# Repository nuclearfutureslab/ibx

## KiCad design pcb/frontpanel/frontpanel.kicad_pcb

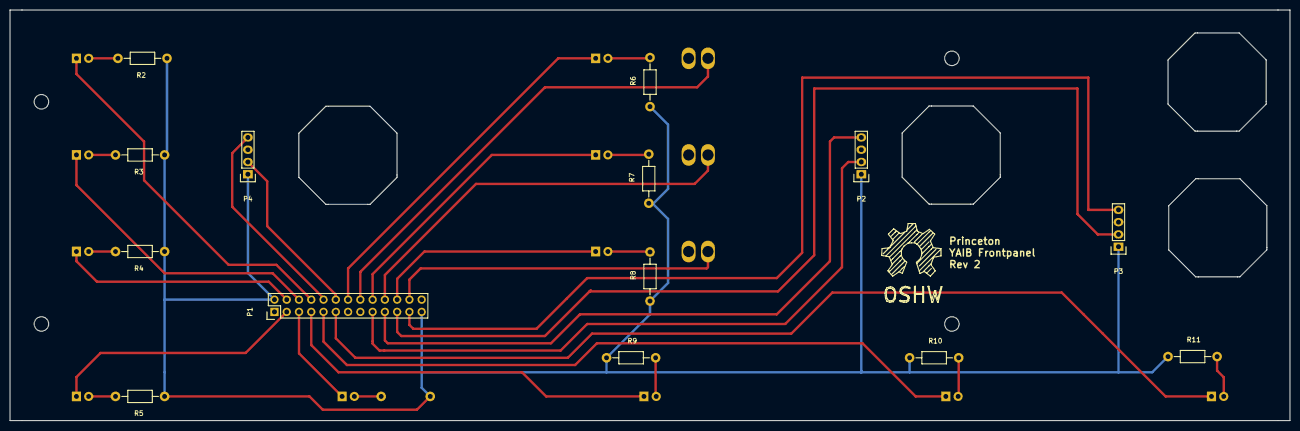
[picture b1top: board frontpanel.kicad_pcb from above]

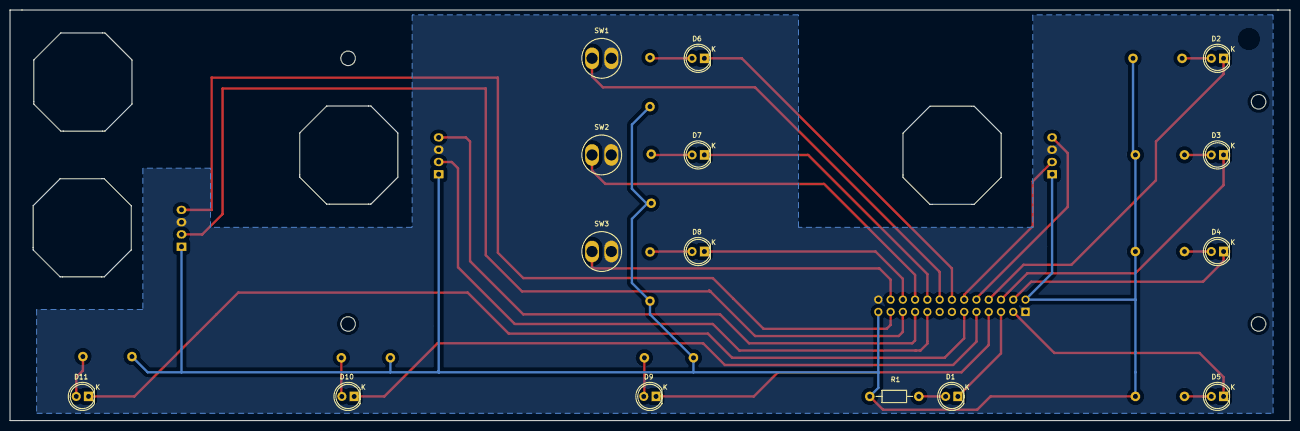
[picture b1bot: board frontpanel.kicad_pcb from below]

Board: 2 copper layers, 265.0 x 85.0 mm, 29 parts (15 on the bottom side), 33 nets.

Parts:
D1: BUI; LED-5MM
D2: T1M; LED-5MM
D3: T2M; LED-5MM
D4: T3M; LED-5MM
D5: MML; LED-5MM
D6: A1L; LED-5MM
D7: A2L; LED-5MM
D8: A3L; LED-5MM
D9: BUA; LED-5MM
D10: BUC; LED-5MM
D11: REA; LED-5MM
P1: CONN_02X13; Pin_Header_Straight_2x13
P2: CALIBRATE; Pin_Header_Straight_1x04
P3: HV; Pin_Header_Straight_1x04
P4: INSPECT; Pin_Header_Straight_1x04
R1, R2, R3, R4, R5, R6, R7, R8, R9, R10, R11: R; Resistor_Horizontal_RM10mm
SW1: A1B; button-panel
SW2: A2B; button-panel
SW3: A3B; button-panel

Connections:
+5V: P1.2, P1.25, P2.1, P3.1, P4.1, R1.1, R2.1, R3.1, R4.1, R5.1, R6.1, R7.1, R8.1, R9.1, R10.1, R11.1
GND: P1.1, P1.26, P2.3, P3.3, P4.3, SW1.2, SW2.2, SW3.2
unnamed: D1.1, P1.5
unnamed: D1.2, R1.2
unnamed: D2.1, P1.8
unnamed: D2.2, R2.2
unnamed: D3.1, P1.6
unnamed: D3.2, R3.2
unnamed: D4.1, P1.4
unnamed: D4.2, R4.2
unnamed: D5.1, P1.3
unnamed: D5.2, R5.2
unnamed: D6.1, P1.14
unnamed: D6.2, R6.2
unnamed: D7.1, P1.18
unnamed: D7.2, R7.2
unnamed: D8.1, P1.22
unnamed: D8.2, R8.2
unnamed: D9.1, P1.7
unnamed: D9.2, R9.2
unnamed: D10.1, P1.9
unnamed: D10.2, R10.2
unnamed: D11.1, P1.11
unnamed: D11.2, R11.2
unnamed: P1.10, P4.4
unnamed: P1.12, P4.2
unnamed: P1.16, SW1.1
unnamed: P1.17, P2.2
unnamed: P1.19, P2.4
unnamed: P1.20, SW2.1
unnamed: P1.21, P3.2
unnamed: P1.23, P3.4
unnamed: P1.24, SW3.1

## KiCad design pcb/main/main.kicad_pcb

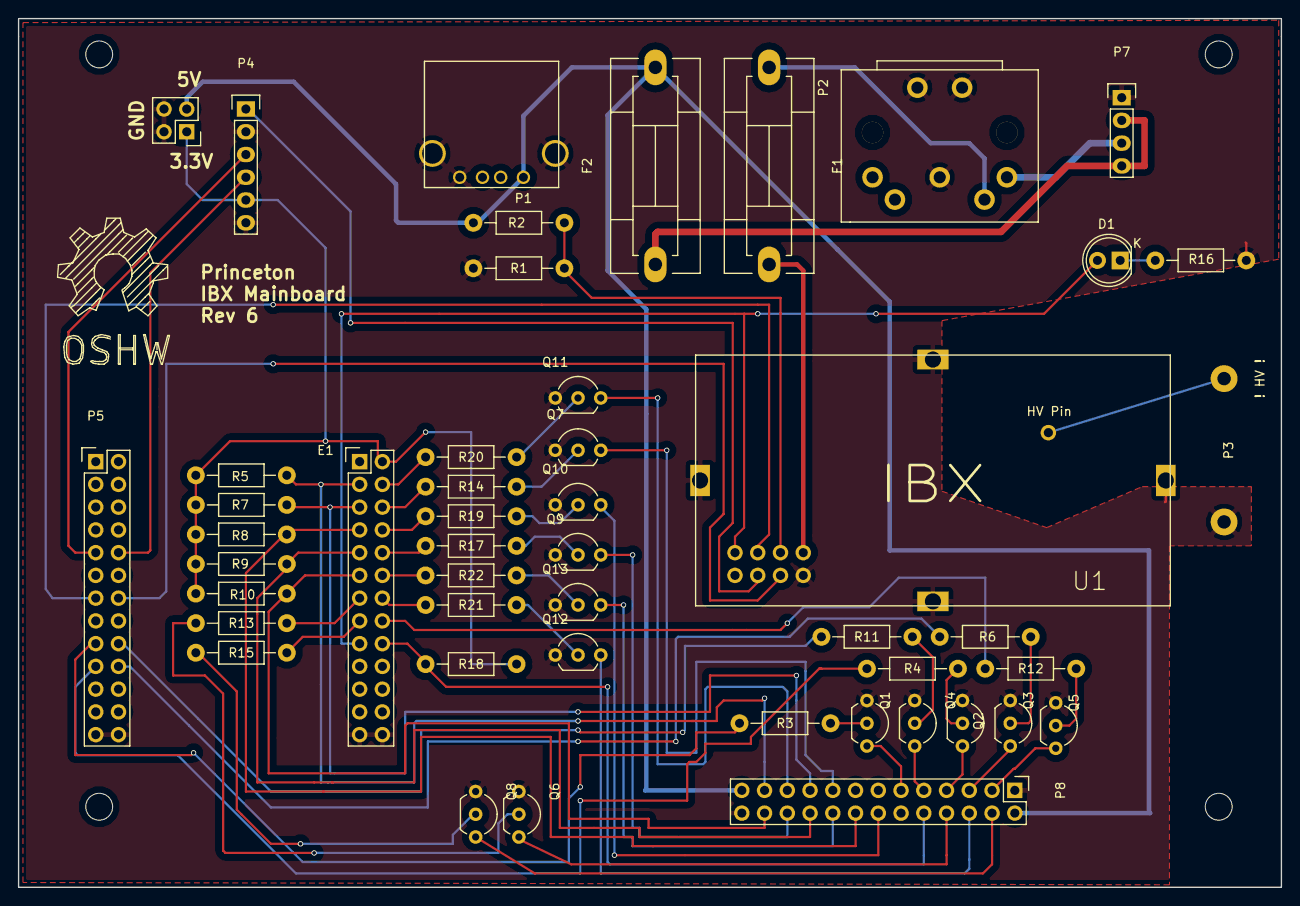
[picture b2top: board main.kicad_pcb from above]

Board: 2 copper layers, 141.0 x 97.0 mm, 48 parts (0 on the bottom side), 61 nets.

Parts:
D1: LED; LED-5MM
E1: CONN_02X13; Pin_Header_Straight_2x13
F1, F2: FUSE; Fuseholder5x20_horiz_SemiClosed_Casing10x25mm
P1: USB_A
P2: DIN_5_GND; DIN-Switchcraft
P3: BNC
P4: CONN_01X06; Pin_Header_Straight_1x06
P5, P8: CONN_02X13; Pin_Header_Straight_2x13
P6: CONN_02X02; Pin_Header_Straight_2x02
P7: CONN_01X04; Pin_Header_Straight_1x04
Q1: REA; TO-92_Inline_Wide
Q2: BUA; TO-92_Inline_Wide
Q3: BUI; TO-92_Inline_Wide
Q4: BUC; TO-92_Inline_Wide
Q5: MML; TO-92_Inline_Wide
Q6: T1M; TO-92_Inline_Wide
Q7: CAL; TO-92_Inline_Wide
Q8: T3M; TO-92_Inline_Wide
Q9: A2L; TO-92_Inline_Wide
Q10: A1L; TO-92_Inline_Wide
Q11: HVL; TO-92_Inline_Wide
Q12: T2M; TO-92_Inline_Wide
Q13: A3L; TO-92_Inline_Wide
R1, R2: 1k; Resistor_Horizontal_RM10mm
R3, R4, R5, R6, R7, R8, R9, R10, R11, R12, R13, R14, R15, R16, R17, R18, R19, R20, R21, R22: R; Resistor_Horizontal_RM10mm
U1: CHV; CHV-rev2

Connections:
+3V3: E1.2, P4.5, P6.1, R5.2, R7.2, R8.2, R9.2, R10.2, R18.2
+5V: F2.2, P1.1, P6.3, P8.2, P8.25, R1.2
+12V: F1.2, U1.7
GND: E1.25, E1.26, P1.4, P1.5, P2.2, P2.GND, P3.2, P4.2, P4.6, P5.25, P5.26, P6.2, P6.4, P7.1, P8.1, P8.26, Q1.1, Q2.1, Q3.1, Q4.1, Q5.1, Q6.1, Q7.1, Q8.1, Q9.1, Q10.1, Q11.1, Q12.1, Q13.1, R2.1, R16.2, U1.8, U1.S1, U1.S2, U1.S3, U1.S4
unnamed: D1.1, R16.1
unnamed: D1.2, E1.17, U1.1
unnamed: E1.3, P8.23, R5.1
unnamed: E1.4, R20.1
unnamed: E1.5, P8.19, R7.1
unnamed: E1.6, R14.1
unnamed: E1.7, P8.16, R8.1
unnamed: E1.8, R19.1
unnamed: E1.9, P8.20, R9.1
unnamed: E1.10, R17.1
unnamed: E1.11, P8.24, R10.1
unnamed: E1.12, R22.1
unnamed: E1.13, R13.1
unnamed: E1.14, R21.1
unnamed: E1.15, R15.1
unnamed: E1.16, R12.1
unnamed: E1.18, P8.10, R18.1
unnamed: F1.1, P2.5
unnamed: F2.1, P7.2, P7.4
unnamed: P2.3, P7.3
unnamed: P3.1, U1.9
unnamed: P4.1, U1.4
unnamed: P4.3, P5.9
unnamed: P4.4, P5.10
unnamed: P5.13, U1.3
unnamed: P5.14, U1.6
unnamed: P5.17, R3.1
unnamed: P5.18, R11.1
unnamed: P5.19, R4.1
unnamed: P5.20, R6.1
unnamed: P8.3, Q5.3
unnamed: P8.4, Q8.3
unnamed: P8.5, Q3.3
unnamed: P8.6, Q12.3
unnamed: P8.7, Q2.3
unnamed: P8.8, Q6.3
unnamed: P8.9, Q4.3
unnamed: P8.11, Q1.3
unnamed: P8.14, Q10.3
unnamed: P8.17, Q7.3
unnamed: P8.18, Q13.3
unnamed: P8.21, Q11.3
unnamed: P8.22, Q9.3
unnamed: Q1.2, R3.2
unnamed: Q2.2, R4.2
unnamed: Q3.2, R6.2
unnamed: Q4.2, R11.2
unnamed: Q5.2, R12.2
unnamed: Q6.2, R13.2
unnamed: Q7.2, R14.2
unnamed: Q8.2, R15.2
unnamed: Q9.2, R17.2
unnamed: Q10.2, R19.2
unnamed: Q11.2, R20.2
unnamed: Q12.2, R21.2
unnamed: Q13.2, R22.2
unnamed: R1.1, R2.2, U1.5
